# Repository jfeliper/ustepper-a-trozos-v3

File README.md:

# ustepper-a-trozos v3
Es una adaptación del ustepper
adaptada a componentes gordos para poder montarlo a mano.
Usa un arduino nano y componentes smd de tamaño 1206, que se pueden soldar incluso aunque nos vaya fallando la vista.

Esta versión corrige el error de la pista de la NTC que faltaba.
También cambia el direccionamiento del pololu ahora:
STEP es el pin4 del nano
DIR es el pin7
ENA es el pin8 
y las patas par configurar los micropasos son ahora las 11, 12 y 13
He añadido unos leds smd para ver el estado de dichos micropaos.

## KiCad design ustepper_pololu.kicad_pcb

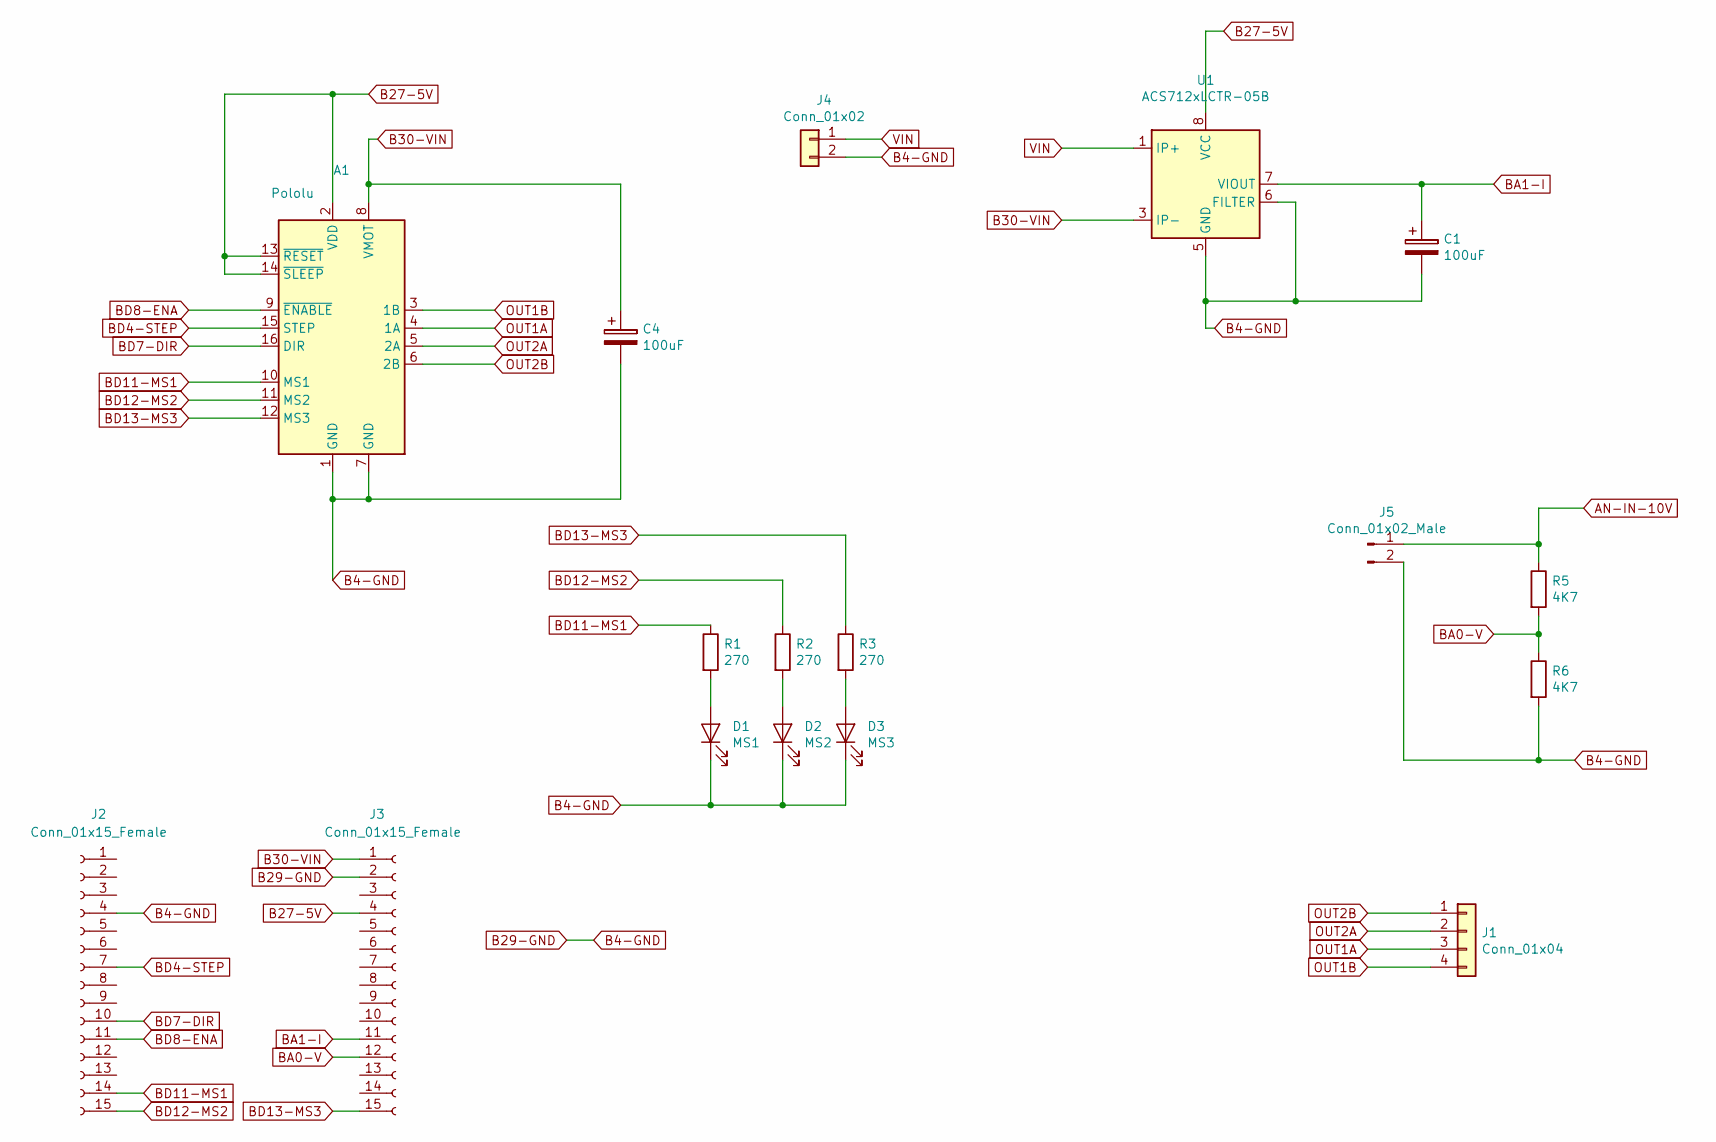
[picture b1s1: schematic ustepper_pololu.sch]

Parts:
A1: Pololu; Pololu_Breakout-16_15.2x20.3mm
C1: 100uF; C_1206_3216Metric_Pad1.42x1.75mm_HandSolder
C4: 100uF; CP_Radial_D6.3mm_P2.50mm
D1: MS1; LED_1206_3216Metric_Pad1.42x1.75mm_HandSolder
D2: MS2; LED_1206_3216Metric_Pad1.42x1.75mm_HandSolder
D3: MS3; LED_1206_3216Metric_Pad1.42x1.75mm_HandSolder
J1: Conn_01x04; PinHeader_1x04_P2.54mm_Vertical
J2, J3: Conn_01x15_Female; PinHeader_1x15_P2.54mm_Vertical
J4: Conn_01x02; PhoenixContact_MSTBA_2,5_2-G_1x02_P5.00mm_Horizontal
J5: Conn_01x02_Male; PinHeader_1x02_P2.54mm_Vertical
R1, R2, R3: 270; R_1206_3216Metric_Pad1.42x1.75mm_HandSolder
R5, R6: 4K7; R_1206_3216Metric_Pad1.42x1.75mm_HandSolder
U1: ACS712xLCTR-05B; SOIC-8_3.9x4.9mm_P1.27mm

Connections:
AN-IN-10V: J5.1, R5.1
B27-5V: A1.2 (VDD), A1.13 (~RESET), A1.14 (~SLEEP), J3.4, U1.8 (VCC)
B29-GND: A1.1 (GND), A1.7 (GND), C1.2, C4.2, D1.1 (K), D2.1 (K), D3.1 (K), J2.4, J3.2, J4.2, J5.2, R6.2, U1.5 (GND), U1.6 (FILTER)
B30-VIN: A1.8 (VMOT), C4.1, J3.1, U1.3 (IP-), U1.4 (IP-)
BA0-V: J3.12, R5.2, R6.1
BA1-I: C1.1, J3.11, U1.7 (VIOUT)
BD4-STEP: A1.15 (STEP), J2.7
BD7-DIR: A1.16 (DIR), J2.10
BD8-ENA: A1.9 (~ENABLE), J2.11
BD11-MS1: A1.10 (MS1), J2.14, R1.1
BD12-MS2: A1.11 (MS2), J2.15, R2.1
BD13-MS3: A1.12 (MS3), J3.15, R3.1
unnamed: D1.2 (A), R1.2
unnamed: D2.2 (A), R2.2
unnamed: D3.2 (A), R3.2
OUT1A: A1.4 (1A), J1.3
OUT1B: A1.3 (1B), J1.4
OUT2A: A1.5 (2A), J1.2
OUT2B: A1.6 (2B), J1.1
VIN: J4.1, U1.1 (IP+), U1.2 (IP+)

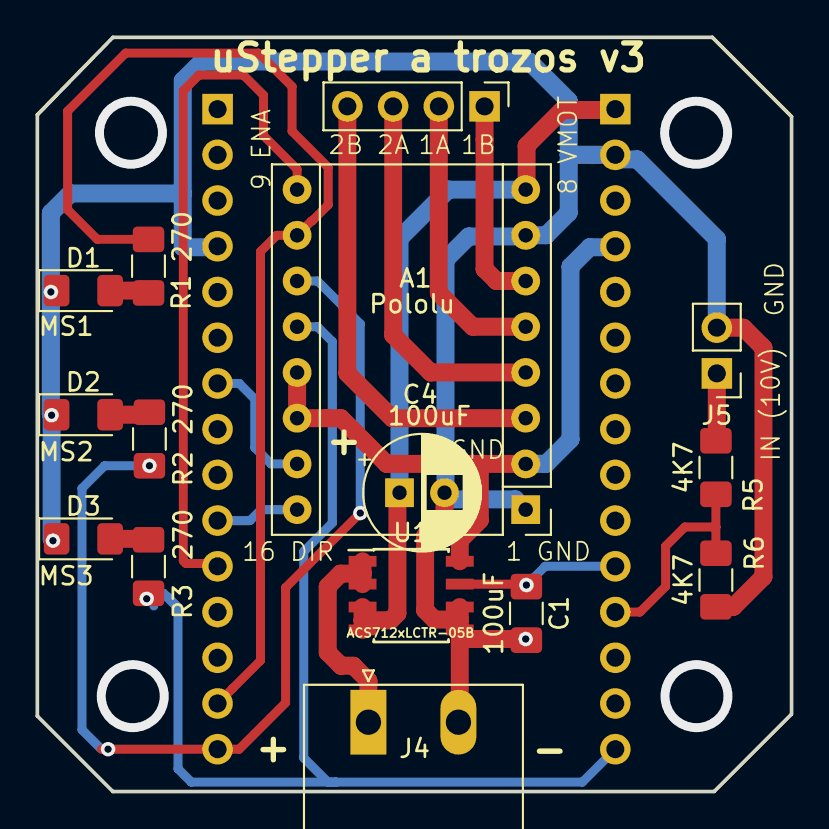
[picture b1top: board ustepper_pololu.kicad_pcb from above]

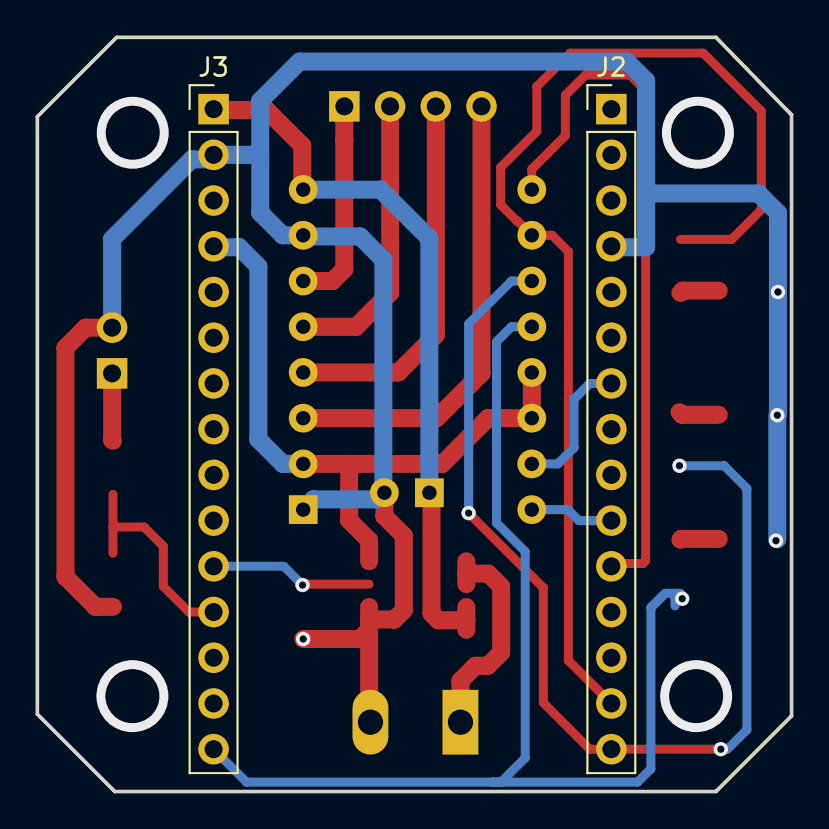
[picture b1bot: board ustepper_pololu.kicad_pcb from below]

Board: 2 copper layers, 41.9 x 41.9 mm, 17 parts (2 on the bottom side), 20 nets.

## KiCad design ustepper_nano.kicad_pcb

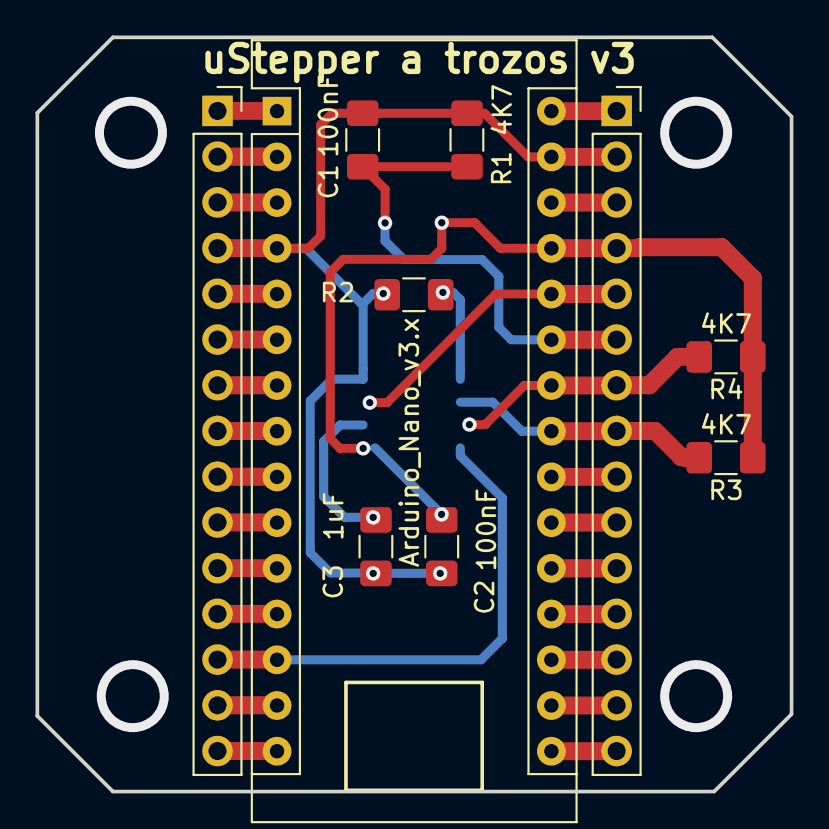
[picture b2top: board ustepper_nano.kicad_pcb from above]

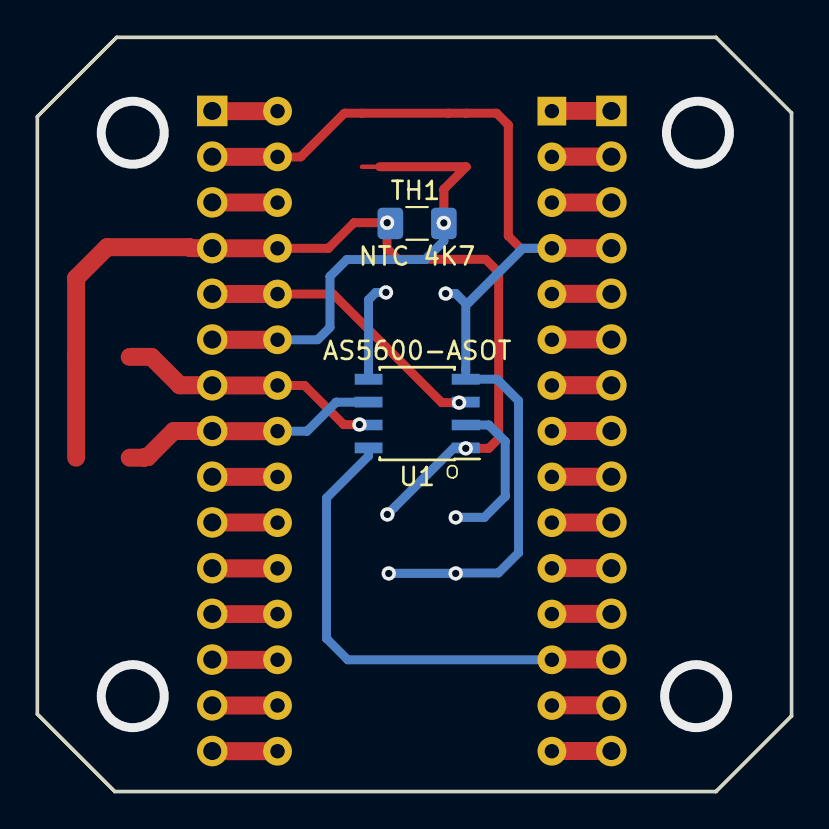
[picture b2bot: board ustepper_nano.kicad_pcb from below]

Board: 2 copper layers, 41.9 x 41.9 mm, 12 parts (2 on the bottom side), 31 nets.

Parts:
A2: Arduino_Nano_v3.x; Arduino_Nano
C1, C2: 100nF; C_1206_3216Metric_Pad1.42x1.75mm_HandSolder
C3: 1uF; C_1206_3216Metric_Pad1.42x1.75mm_HandSolder
J6, J7: Conn_01x15_Female; PinSocket_1x15_P2.54mm_Vertical
R1, R3, R4: 4K7; R_1206_3216Metric_Pad1.42x1.75mm_HandSolder
R2: R; R_1206_3216Metric_Pad1.42x1.75mm_HandSolder
TH1: NTC 4K7; R_1206_3216Metric_Pad1.42x1.75mm_HandSolder
U1: AS5600-ASOT; SOIC-8_3.9x4.9mm_P1.27mm

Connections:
3-RST: A2.3, J6.3
17-3V3: A2.17, J7.14
18-AREF: A2.18, J7.13
27-5V: A2.27, C2.1, J7.4, R3.1, R4.1, TH1.1, U1.1
28-RST: A2.28, J7.3
29-GND: A2.4, A2.29, C1.2, C2.2, C3.2, J6.4, J7.2, R1.2, R2.2, U1.4
30-VIN: A2.30, J7.1
A0-: A2.19, J7.12
A1-: A2.20, J7.11
A2-: A2.21, J7.10
A3-: A2.22, J7.9
A4-SDA: A2.23, J7.8, R3.2, U1.6
A5-SCL: A2.24, J7.7, R4.2, U1.7
A6-TEMP: A2.25, C1.1, J7.6, R1.1, TH1.2
A7-ASA: A2.26, J7.5, U1.3
D0-RXD: A2.2, J6.2
D1-TXD: A2.1, J6.1
D2-: A2.5, J6.5
D3-: A2.6, J6.6
D4-STEP: A2.7, J6.7
D5-: A2.8, J6.8
D6-: A2.9, J6.9
D7-DIR: A2.10, J6.10
D8-ENA: A2.11, J6.11
D9-: A2.12, J6.12
D10-ASDIR: A2.13, J6.13, U1.8
D11-MS1: A2.14, J6.14
D12-MS2: A2.15, J6.15
D13-MS3: A2.16, J7.15
unnamed: C3.1, U1.2
unnamed: R2.1, U1.5
